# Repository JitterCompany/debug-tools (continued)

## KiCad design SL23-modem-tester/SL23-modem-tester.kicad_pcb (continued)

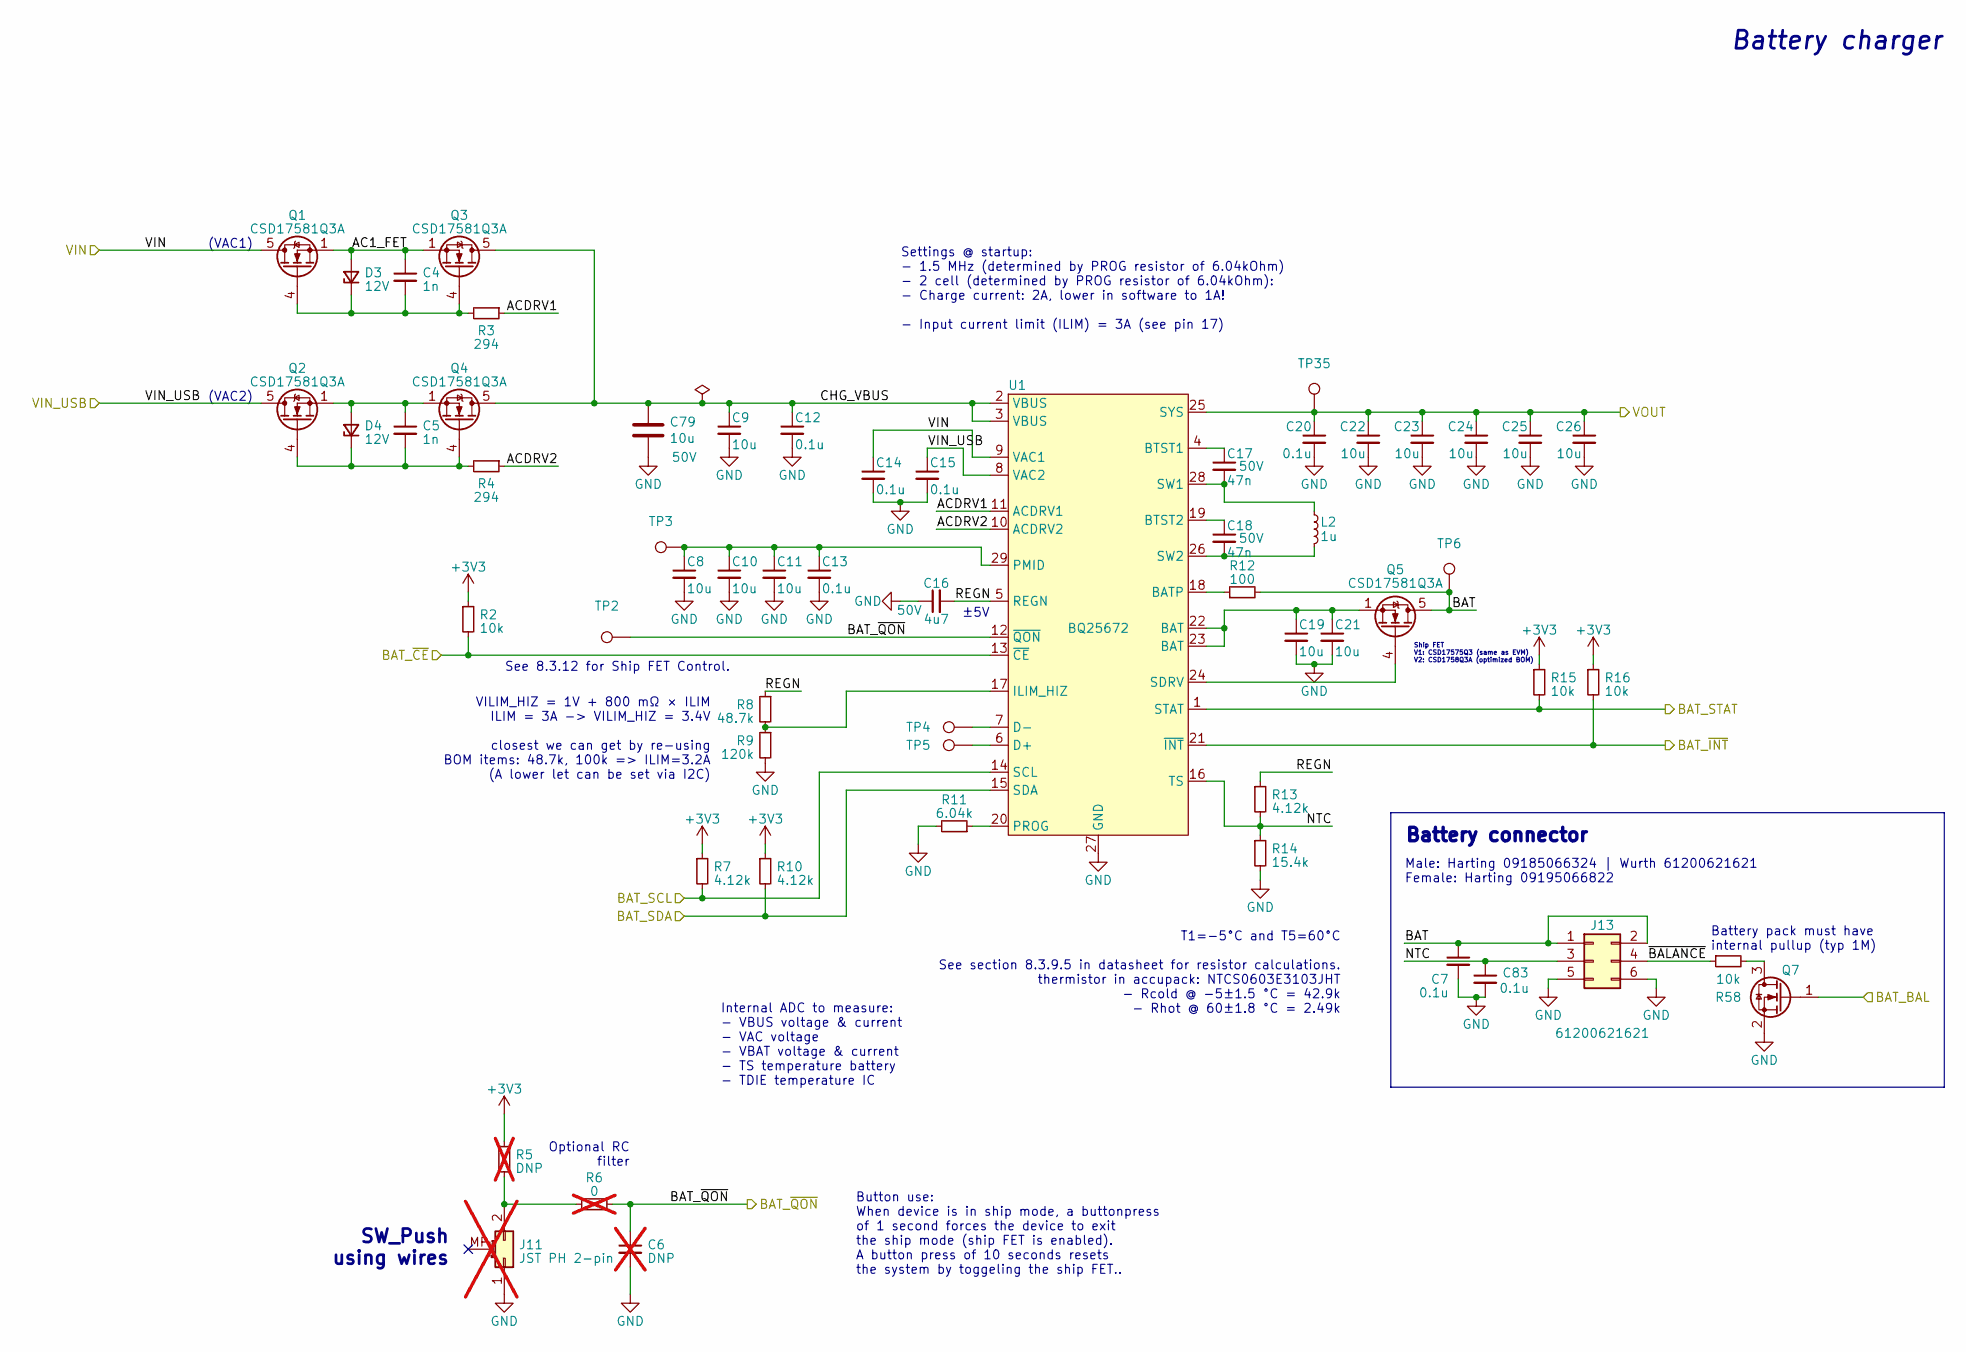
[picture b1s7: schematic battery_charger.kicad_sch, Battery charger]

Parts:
C4, C5: 1n; C_0603_1608Metric; rating 50V; MPN CGA3E2X7R1H102K080AA; Mouser 810-CGA3E2X7R1H102K
C6: DNP; C_0603_1608Metric; not fitted
C7, C12, C13, C14, C15, C20, C83: 0.1u; C_0603_1608Metric; rating 50V; MPN CGA3E2X7R1H104K080AA; Mouser 810-CGA3E2X7R1H104K
C8, C9, C10, C11, C19, C21, C22, C23, C24, C25, C26: 10u; C_0805_2012Metric; rating 50V; MPN GRM21BR61H106KE43L; Mouser 81-GRM21BR61H106KE3L
C16: 4u7; C_0805_2012Metric; rating 50V; MPN GRM21BZ71H475KE15K; Mouser 81-GRM21BZ71H475KE5K
C17, C18: 47n; C_0603_1608Metric; rating 50V; MPN CGA3E2X7R1H473K080AA; Mouser 810-CGA3E2X7R1H473K
C79: 10u; C_1210_3225Metric; rating 50V; MPN CL32A106KBJNNNE; Mouser 187-CL32A106KBJNNNE
D3, D4: 12V; D_SOD-523; MPN BZT52C12T-7; Mouser 621-BZT52C12T-7
J11: JST PH 2-pin; JST_PH_B2B-PH-SM4-TB_1x02-1MP_P2.00mm_Vertical; MPN B2B-PH-SM4-TB; Farnell 9492534; not fitted
J13: 61200621621; IDC_Header_2x03_P2.54mm_Vertical_Male; MPN 61200621621; Mouser 710-61200621621
L2: 1u; L_TDK_SPM6530; MPN SPM6530T-1R0M120; Mouser 810-SPM6530T-1R0M120
Q1, Q2, Q3, Q4, Q5: CSD17581Q3A; CSD17552Q3A; MPN CSD17581Q3A; Mouser 595-CSD17581Q3A
Q7: BSS138BK,215; SOT-23; MPN BSS138BK,215; Farnell 2053833
R2, R15, R16, R58: 10k; R_0603_1608Metric; rating 1%; MPN CRCW060310K0FKEAHP; Mouser 71-CRCW060310K0FKEAH
R3, R4: 294; R_0603_1608Metric; rating 1%; MPN CRCW0603294RFKEA; Mouser 71-CRCW0603-294-E3
R5: DNP; R_0603_1608Metric; not fitted
R6: 0; R_0603_1608Metric; rating 1%; MPN RC0603FR-070RL; Mouser 603-RC0603FR-070RL; not fitted
R7, R10, R13: 4.12k; R_0603_1608Metric; rating 1%
R8: 48.7k; R_0603_1608Metric; rating 1%
R9: 120k; R_0603_1608Metric; rating 1%
R11: 6.04k; R_0603_1608Metric; rating 1%; MPN CRCW06036K04FKEAC; Mouser 71-CRCW06036K04FKEAC
R12: 100; R_0603_1608Metric; rating 1%; MPN CRCW0603100RFKEAC; Mouser 71-CRCW0603100RFKEAC
R14: 15.4k; R_0603_1608Metric; rating 1%; MPN CRCW060315K4FKEB; Mouser 71-CRCW060315K4FKEB
TP2, TP3, TP6, TP35: TestPoint; TestPoint_THTPad_D1.0mm_Drill0.5mm
TP4, TP5: TestPoint; TestPoint_Pad_D1.0mm
U1: BQ25672; TI_VQFN-HR-29-RQM; MPN BQ25672RQMR; Mouser 595-BQ25672RQMR

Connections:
+3V3: R2.1, R5.1, R7.1, R10.1, R15.1, R16.1; also elsewhere on the board
/BAT_BAL: Q7.1 (G); also elsewhere on the board
/BAT_SCL: R7.2, U1.14 (SCL); also elsewhere on the board
/BAT_SDA: R10.2, U1.15 (SDA); also elsewhere on the board
/BAT_STAT: R15.2, U1.1 (STAT); also elsewhere on the board
/BAT_~CE: R2.2, U1.13 (~CE); also elsewhere on the board
/BAT_~INT: R16.2, U1.21 (~INT); also elsewhere on the board
/BAT_~QON: C6.1, R6.2, TP2.1 (1_1), U1.12 (~QON); also elsewhere on the board
/Battery Charger/AC1_FET: C4.1, D3.2 (A), Q1.1 (S), Q1.2 (S), Q1.3 (S), Q3.1 (S), Q3.2 (S), Q3.3 (S)
/Battery Charger/ACDRV1: R3.1, U1.11 (ACDRV1)
/Battery Charger/ACDRV2: R4.1, U1.10 (ACDRV2)
/Battery Charger/BAT: C7.1, J13.1, J13.2, Q5.5 (D), R12.2, TP6.1 (1_1)
/Battery Charger/CHG_VBUS: C9.1, C12.1, C79.1, Q3.5 (D), Q4.5 (D), U1.2 (VBUS), U1.3 (VBUS)
/Battery Charger/NTC: C83.1, J13.3, R13.2, R14.1, U1.16 (TS)
/Battery Charger/REGN: C16.2, R8.1, R13.1, U1.5 (REGN)
/Battery Charger/VIN: C14.1, Q1.5 (D), U1.9 (VAC1); also elsewhere on the board
/Battery Charger/~BALANCE: J13.4, R58.1
/VSYS: C20.1, C22.1, C23.1, C24.1, C25.1, C26.1, TP35.1 (1_1), U1.25 (SYS); also elsewhere on the board
GND: C6.2, C7.2, C8.2, C9.2, C10.2, C11.2, C12.2, C13.2, C14.2, C15.2, C16.1, C19.2, C20.2, C21.2, C22.2, C23.2, C24.2, C25.2, C26.2, C79.2, C83.2, J11.1, J13.5, J13.6, Q7.2 (S), R9.2, R11.2, R14.2, U1.27 (GND); also elsewhere on the board
unnamed: C19.1, C21.1, Q5.1 (S), Q5.2 (S), Q5.3 (S), U1.22 (BAT), U1.23 (BAT)
unnamed: C4.2, D3.1 (K), Q1.4 (G), Q3.4 (G), R3.2
unnamed: C5.1, D4.2 (A), Q2.1 (S), Q2.2 (S), Q2.3 (S), Q4.1 (S), Q4.2 (S), Q4.3 (S)
unnamed: C5.2, D4.1 (K), Q2.4 (G), Q4.4 (G), R4.2
unnamed: J11.2, R5.2, R6.1
unnamed: Q5.4 (G), U1.24 (SDRV)
unnamed: Q7.3 (D), R58.2
unnamed: R12.1, U1.18 (BATP)
unnamed: C17.1, U1.4 (BTST1)
unnamed: C18.1, U1.19 (BTST2)
unnamed: TP5.1 (1_1), U1.6 (D+)
unnamed: TP4.1 (1_1), U1.7 (D-)
unnamed: R8.2, R9.1, U1.17 (ILIM_HIZ)
unnamed: C8.1, C10.1, C11.1, C13.1, TP3.1 (1_1), U1.29 (PMID)
unnamed: R11.1, U1.20 (PROG)
unnamed: C17.2, L2.1, U1.28 (SW1)
unnamed: C18.2, L2.2, U1.26 (SW2)
VBUS: C15.1, Q2.5 (D), U1.8 (VAC2); also elsewhere on the board

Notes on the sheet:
Internal ADC to measure: - VBUS voltage & current - VAC voltage - VBAT voltage & current - TS temperature battery - TDIE temperature IC
Optional RC filter
SW_Push using wires
Button use: When device is in ship mode, a buttonpress of 1 second forces the device to exit the ship mode (ship FET is enabled). A button press of 10 seconds resets the system by toggeling the ship FET..
(VAC1)
T1=-5°C and T5=60°C See section 8.3.9.5 in datasheet for resistor calculations. thermistor in accupack: NTCS0603E3103JHT - Rcold @ -5±1.5 °C = 42.9k - Rhot @ 60±1.8 °C = 2.49k
Male: Harting 09185066324 | Wurth 61200621621 Female: Harting 09195066822
(VAC2)
Ship FET V1: CSD17575Q3 (same as EVM) V2: CSD1758Q3A (optimized BOM)
±5V
VILIM_HIZ = 1V + 800 mΩ × ILIM ILIM = 3A -> VILIM_HIZ = 3.4V closest we can get by re-using BOM items: 48.7k, 100k => ILIM=3.2A (A lower let can be set via I2C)
Battery pack must have internal pullup (typ 1M)
See 8.3.12 for Ship FET Control.
Battery charger
Battery connector
Settings @ startup: - 1.5 MHz (determined by PROG resistor of 6.04kOhm) - 2 cell (determined by PROG resistor of 6.04kOhm): - Charge current: 2A, lower in software to 1A! - Input current limit (ILIM) = 3A (see pin 17)

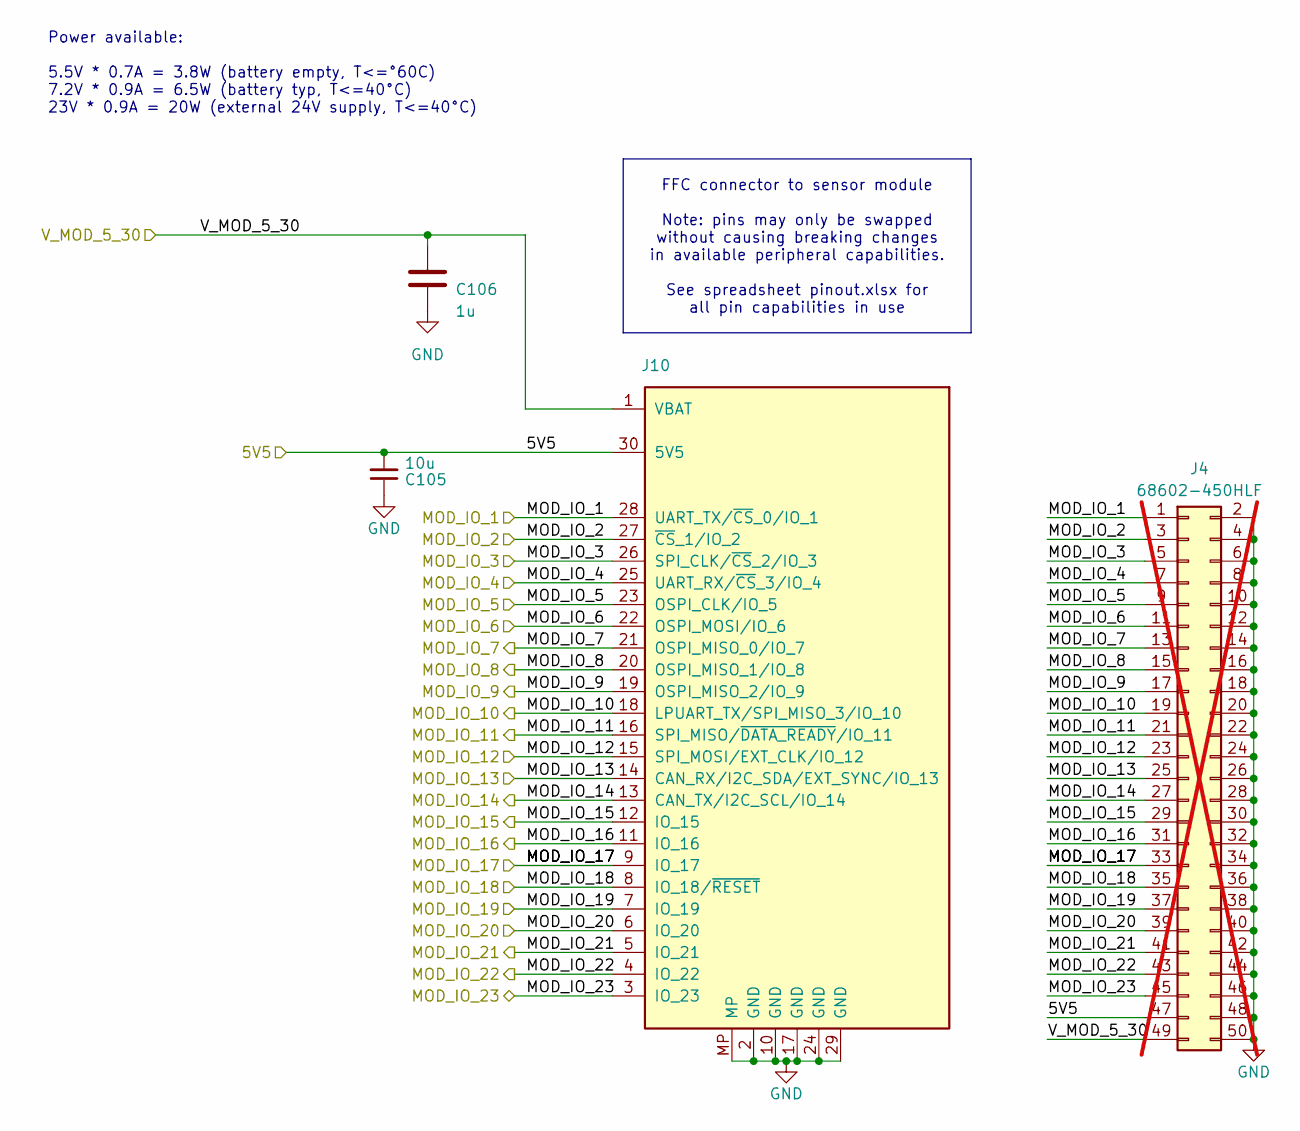
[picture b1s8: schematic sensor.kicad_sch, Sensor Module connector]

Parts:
C105: 10u; C_0805_2012Metric; rating 50V; MPN GRM21BR61H106KE43L; Mouser 81-GRM21BR61H106KE3L
C106: 1u; C_0603_1608Metric; rating 35V; MPN CGA3E1X7R1V105K080AC; Mouser 810-CGA3E1X7R1V105KC
J4: 68602-450HLF; PinHeader_2x25_P2.54mm_Vertical; MPN 68602-450HLF; not fitted
J10: Conn_01x30; Hirose_FH12-30S-0.5SH_1x15-1MP_P0.50mm_Horizontal; MPN FH12-30S-0.5SH(55); Mouser 798-FH12-30S-0.5SH55

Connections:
+5V5: C105.2, J4.47, J10.30 (5V5); also elsewhere on the board
/MCU/MOD_IO_1: J4.1, J10.28 (UART_TX/~CS_0/IO_1); also elsewhere on the board
/MCU/MOD_IO_2: J4.3, J10.27 (~CS_1/IO_2); also elsewhere on the board
/MCU/MOD_IO_3: J4.5, J10.26 (SPI_CLK/~CS_2/IO_3); also elsewhere on the board
/MCU/MOD_IO_4: J4.7, J10.25 (UART_RX/~CS_3/IO_4); also elsewhere on the board
/MCU/MOD_IO_5: J4.9, J10.23 (OSPI_CLK/IO_5); also elsewhere on the board
/MCU/MOD_IO_6: J4.11, J10.22 (OSPI_MOSI/IO_6); also elsewhere on the board
/MCU/MOD_IO_7: J4.13, J10.21 (OSPI_MISO_0/IO_7); also elsewhere on the board
/MCU/MOD_IO_8: J4.15, J10.20 (OSPI_MISO_1/IO_8); also elsewhere on the board
/MCU/MOD_IO_9: J4.17, J10.19 (OSPI_MISO_2/IO_9); also elsewhere on the board
/MCU/MOD_IO_10: J4.19, J10.18 (LPUART_TX/SPI_MISO_3/IO_10); also elsewhere on the board
/MCU/MOD_IO_11: J4.21, J10.16 (SPI_MISO/~DATA_READY/IO_11); also elsewhere on the board
/MCU/MOD_IO_12: J4.23, J10.15 (SPI_MOSI/EXT_CLK/IO_12); also elsewhere on the board
/MCU/MOD_IO_13: J4.25, J10.14 (CAN_RX/I2C_SDA/EXT_SYNC/IO_13); also elsewhere on the board
/MCU/MOD_IO_14: J4.27, J10.13 (CAN_TX/I2C_SCL/IO_14); also elsewhere on the board
/MCU/MOD_IO_15: J4.29, J10.12 (IO_15); also elsewhere on the board
/MCU/MOD_IO_16: J4.31, J10.11 (IO_16); also elsewhere on the board
/MCU/MOD_IO_17: J4.33, J10.9 (IO_17); also elsewhere on the board
/MCU/MOD_IO_18: J4.35, J10.8 (IO_18/~RESET); also elsewhere on the board
/MCU/MOD_IO_19: J4.37, J10.7 (IO_19); also elsewhere on the board
/MCU/MOD_IO_20: J4.39, J10.6 (IO_20); also elsewhere on the board
/MCU/MOD_IO_21: J4.41, J10.5 (IO_21); also elsewhere on the board
/MCU/MOD_IO_22: J4.43, J10.4 (IO_22); also elsewhere on the board
/MCU/MOD_IO_23: J4.45, J10.3 (IO_23); also elsewhere on the board
/V_MOD_5_30: C106.1, J4.49, J10.1 (VBAT); also elsewhere on the board
GND: C105.1, C106.2, J4.2, J4.4, J4.6, J4.8, J4.10, J4.12, J4.14, J4.16, J4.18, J4.20, J4.22, J4.24, J4.26, J4.28, J4.30, J4.32, J4.34, J4.36, J4.38, J4.40, J4.42, J4.44, J4.46, J4.48, J4.50, J10.2 (GND), J10.10 (GND), J10.17 (GND), J10.24 (GND), J10.29 (GND), J10.MP; also elsewhere on the board

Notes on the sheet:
Power available: 5.5V * 0.7A = 3.8W (battery empty, T<=°60C) 7.2V * 0.9A = 6.5W (battery typ, T<=40°C) 23V * 0.9A = 20W (external 24V supply, T<=40°C)
FFC connector to sensor module Note: pins may only be swapped without causing breaking changes in available peripheral capabilities. See spreadsheet pinout.xlsx for all pin capabilities in use

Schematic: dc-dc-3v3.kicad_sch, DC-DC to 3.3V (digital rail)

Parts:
C42, C43: 10u; C_1210_3225Metric; rating 50V; MPN CL32A106KBJNNNE; Mouser 187-CL32A106KBJNNNE
C44: 4u7; C_0805_2012Metric; rating 50V; MPN GRM21BZ71H475KE15K; Mouser 81-GRM21BZ71H475KE5K
C45: 1u; C_0603_1608Metric; rating 35V; MPN CGA3E1X7R1V105K080AC; Mouser 810-CGA3E1X7R1V105KC
C46, C48: 220n; C_0603_1608Metric; rating 50V; MPN CGA3E3X7R1H224K080AB; Mouser 810-CGA3E3X7R1H224K
C47, C50, C53: 0.1u; C_0603_1608Metric; rating 50V; MPN CGA3E2X7R1H104K080AA; Mouser 810-CGA3E2X7R1H104K
C49: 680p; C_0603_1608Metric; rating 50V; MPN GCM1885C1H681JA16J; Mouser 81-GCM1885C1H681JA6J
C52: 4n7; C_0603_1608Metric; rating 50V; MPN CGA3E2X7R1H472M080AA; Mouser 810-CGA3E2X7R1H472MA
C54, C55: 100u; C_1210_3225Metric; rating 6V3; MPN CL32A107MQVNNNE; Mouser 187-CL32A107MQVNNNE
C56: 47u; C_1210_3225Metric; rating 10V; MPN C3225X5R1A476M250AC; Mouser 810-C3225X5R1A476M; not fitted
C74: 560p; C_0603_1608Metric; rating 50V; MPN GCM188L81H561KA03D; Mouser 81-GCM188L81H561KA3D
C78: 2n7; C_0603_1608Metric; rating 50V; MPN CGA3E2C0G1H272J080AE; Mouser 810-CGA3E2C0G1H272J8
L4: 8.2uH; L_Wuerth_LHMI_8040; MPN 74437358082; Mouser 710-74437358082
R21, R37: 48.7k; R_0603_1608Metric; rating 1%
R28: DNP; R_0603_1608Metric; not fitted
R29: 10k; R_0603_1608Metric; rating 1%
R30: DNI; R_0603_1608Metric; rating 1%; not fitted
R31, R57: 10k; R_0603_1608Metric; rating 1%; MPN CRCW060310K0FKEAHP; Mouser 71-CRCW060310K0FKEAH
R33: 120k; R_0603_1608Metric; rating 1%; MPN CRCW0603120KFKEAC; Mouser 71-CRCW0603120KFKEAC
R34, R56: 348K; R_0603_1608Metric; rating 1%; MPN CRCW0603348KFKEA; Mouser 71-CRCW0603-348K-E3
R35: 2.2; R_0603_1608Metric; rating 1%; MPN CRCW06032R20FKEAC; Mouser 71-CRCW06032R20FKEAC
R36: 4.12k; R_0603_1608Metric; rating 1%
R38: 15.4k; R_0603_1608Metric; rating 1%
TP10, TP11, TP12: TestPoint; TestPoint_THTPad_D1.0mm_Drill0.5mm
U3: SIC473ED-T1-GE3; Vishay_MLP55-27L; MPN SIC473ED-T1-GE3; Mouser 78-SIC473ED-T1-GE3

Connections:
+3V3: C52.1, C53.1, C54.1, C55.1, C56.1, L4.2, R37.1, TP11.1 (1_1); also elsewhere on the board
/DCDC_ULTRA: R57.1; also elsewhere on the board
/POWER_GOOD_3V3: U3.2 (PGOOD); also elsewhere on the board
/Power 3V3/BOOT: C50.1, U3.4 (BOOT)
/Power 3V3/CMP: R34.1, U3.21 (COMP)
/Power 3V3/EN: R28.1, R29.2, R30.1, TP10.1 (1_1), U3.3 (EN)
/Power 3V3/FB: R37.2, R38.1, U3.22 (FB)
/Power 3V3/FSW: R21.1, R56.1, U3.24 (FSW)
/Power 3V3/ILIMIT: R33.1, U3.25 (ILIMIT)
/Power 3V3/MODE: R31.1, U3.27 (MODE)
/Power 3V3/PHASE: R35.2, U3.5 (PHASE), U3.6 (PHASE)
/Power 3V3/SS: C47.1, U3.19 (SS)
/Power 3V3/SW: L4.1, R36.2, U3.12 (SW), U3.13 (SW), U3.14 (SW)
/Power 3V3/VDD: C45.2, U3.26 (VDD)
/Power 3V3/VDRV: C44.2, U3.16 (VDRV)
/Power 3V3/VSNS: C74.1, C78.2, U3.20 (VSNS)
/Power 3V3/~DISABLE: R28.2
/VSYS: C42.1, C43.1, C46.1, C48.1, R29.1, U3.1 (VCIN), U3.7 (VIN), U3.8 (VIN), U3.29 (VIN); also elsewhere on the board
GND: C42.2, C43.2, C44.1, C45.1, C46.2, C47.2, C48.2, C49.2, C53.2, C54.2, C55.2, C56.2, R21.2, R30.2, R31.2, R33.2, R38.2, R56.2, TP12.1 (1_1), U3.9 (PGND), U3.10 (PGND), U3.11 (PGND), U3.17 (PGND), U3.23 (AGND), U3.28 (AGND), U3.30 (PGND); also elsewhere on the board
unnamed: C49.1, R34.2
unnamed: C50.2, R35.1
unnamed: C52.2, C74.2, C78.1, R36.1
unnamed: R57.2, U3.18 (ULTRASONIC)

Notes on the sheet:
DC-DC converter 5.5-30V in to 3.3V 3A out
ESR compensation
Soft-start 100nF = 16 ms
3V3 DC-DC
Settings: Power save mode, 400kHz, 5A peak limit
DC-derating: 8uF @30V, 16.5uF @12V
Output voltage setpoint Fb=0.8V > 3.33V
Note: open-drain output. needs pull-up, is located on MCU sheet.
Set high to force frequency above audio range (>20khz) in case the vibrations from switching impact the sensor readings
Note: DC-bias derated to 3x35uF @3.3V
Click to go back to power input
Compensation network Fco=58.9kHz, pm=80.9deg (Vishay PowerCAD)
No UVLO: threshold is not accurate Firmware can periodically measure the battery level and stop measuring if it becomes too low
EN pin is high voltage compatible

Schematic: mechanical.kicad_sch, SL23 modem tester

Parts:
FID1, FID2, FID3, FID4, FID5: Fiducial; Fiducial_1mm_Mask3mm
H1, H3, H4: MountingHole; MountingHole_3.2mm_M3_DIN965_Pad
H2: MountingHole_Pad; MountingHole_3.2mm_M3_DIN965_Pad
LOGO1: Jitter front; Jitter
LOGO2: Jitter back; Jitter

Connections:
GND: H1.1 (1_1), H2.1 (1_1), H3.1 (1_1), H4.1 (1_1); also elsewhere on the board

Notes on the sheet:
Top
Mounting Holes
Mechanical
Logos on PCB
Fiducials

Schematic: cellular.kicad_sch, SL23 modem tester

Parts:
C90, C91, C96: 0.1u; C_0603_1608Metric; rating 50V; MPN CGA3E2X7R1H104K080AA; Mouser 810-CGA3E2X7R1H104K
C92: 4n7; C_0603_1608Metric; rating 50V; MPN CGA3E2X7R1H472M080AA; Mouser 810-CGA3E2X7R1H472MA
C93, C95: 100u; C_1210_3225Metric; rating 6V3; MPN CL32A107MQVNNNE; Mouser 187-CL32A107MQVNNNE
C94: 4u7; C_0805_2012Metric; rating 50V; MPN GRM21BZ71H475KE15K; Mouser 81-GRM21BZ71H475KE5K
H3D1: 4G Modem; mPCIe_module
J2: MM60-EZH039-B5-R850; MPN MM60-EZH039-B5-R850; Mouser 656-MM60-EZH039-B5-R
J6: PinHeader_2x20_P2.54mm_Vertical; not fitted
J7: ‎MM60-52B1-G1-R850‎; BUS_PCI_Express_Mini_MM60-52B1-G1-R850; MPN ‎MM60-52B1-G1-R850‎; Mouser 656-MM6052B1G1R850
R50: DNP; R_0603_1608Metric; not fitted
U6: SLG59M301V; DFN200X150X80-8N; MPN SLG59M301V; Mouser 402-SLG59M301V

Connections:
+3V3: C90.1, C91.1, U6.1 (VDD), U6.3 (IN), U6.4 (IN); also elsewhere on the board
/CELLULAR_DTR: J6.5, J7.31 (PETn0); also elsewhere on the board
/CELLULAR_PWR_EN: R50.1, U6.2 (ON); also elsewhere on the board
/CELLULAR_UART_CTS: J6.1, J7.23 (PERn0); also elsewhere on the board
/CELLULAR_UART_RTS: J6.3, J7.25 (PERp0); also elsewhere on the board
/CELLULAR_UART_RX: J6.19, J7.11 (REFCLK-); also elsewhere on the board
/CELLULAR_UART_TX: J6.17, J7.13 (REFCLK+); also elsewhere on the board
/CELLULAR_~RESET: J6.9, J7.22 (~PERST); also elsewhere on the board
/Cellular Modem/3V3_PCIE: C93.1, C94.1, C95.1, C96.1, J6.39, J7.2 (+3V3AUX), J7.24 (+3V3AUX), J7.39 (+3V3AUX), J7.41 (+3V3AUX), J7.52 (+3V3AUX), U6.5 (VOUT), U6.6 (VOUT)
/Cellular Modem/LED_~WWAN: J6.7, J7.42 (~LED_WWAN)
/Cellular Modem/RI: J6.13, J7.17 (UIM_C8)
/Cellular Modem/UIM_CLK: J6.31, J7.12 (UIM_CLK)
/Cellular Modem/UIM_DATA: J6.33, J7.10 (UIM_DATA)
/Cellular Modem/UIM_VCC: J6.35, J7.8 (UIM_PWR)
/Cellular Modem/UIM_~RST: J6.29, J7.14 (~UIM_RESET)
/Cellular Modem/USB_D+: J6.23, J7.38 (USB_D+)
/Cellular Modem/USB_D-: J6.25, J7.36 (USB_D-)
/Cellular Modem/~W_DISABLE: J6.11, J7.20 (~W_DISABLE)
GND: C90.2, C91.2, C92.2, C93.2, C94.2, C95.2, C96.2, J2.1 (1_1), J6.2, J6.4, J6.6, J6.8, J6.10, J6.12, J6.14, J6.16, J6.18, J6.20, J6.22, J6.24, J6.26, J6.28, J6.30, J6.32, J6.34, J6.36, J6.38, J6.40, J7.4 (GND), J7.9 (GND), J7.15 (GND), J7.18 (GND), J7.21 (GND), J7.26 (GND), J7.27 (GND), J7.29 (GND), J7.34 (GND), J7.35 (GND), J7.37 (GND), J7.40 (GND), J7.43 (GND), J7.50 (GND), J7.MP, R50.2, U6.8 (GND); also elsewhere on the board
unnamed: C92.1, U6.7 (CAP)

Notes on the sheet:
Power switch
mPCIE slot
mPCIE modem should have its own onboard SIM card
For some modules (e.g. Quectel EC2x) this determines if the module is allowed to enter sleep mode (low=never sleep)
On > 0.85V
no SIM slot
Easily serviceable / upgradeable: most modems in mini-PCIe form-factor should work (4G / LTE-M / 5G / etc)
Controls power to mini-PCIE slot
Slew rate control 4.7nF = ca 2.5 V/ms I_{inrush} = 200uF * 2.5 V/ms = 500mA
SLG59M301V has internal pulldown (4M)
Quectel EC25 current: max 800mA, 2.7A peak (2G) mPCIE spec: max 1100mA, 2.75A peak
Cellular
Derating: 2x64uF @ 3.3V
I2C

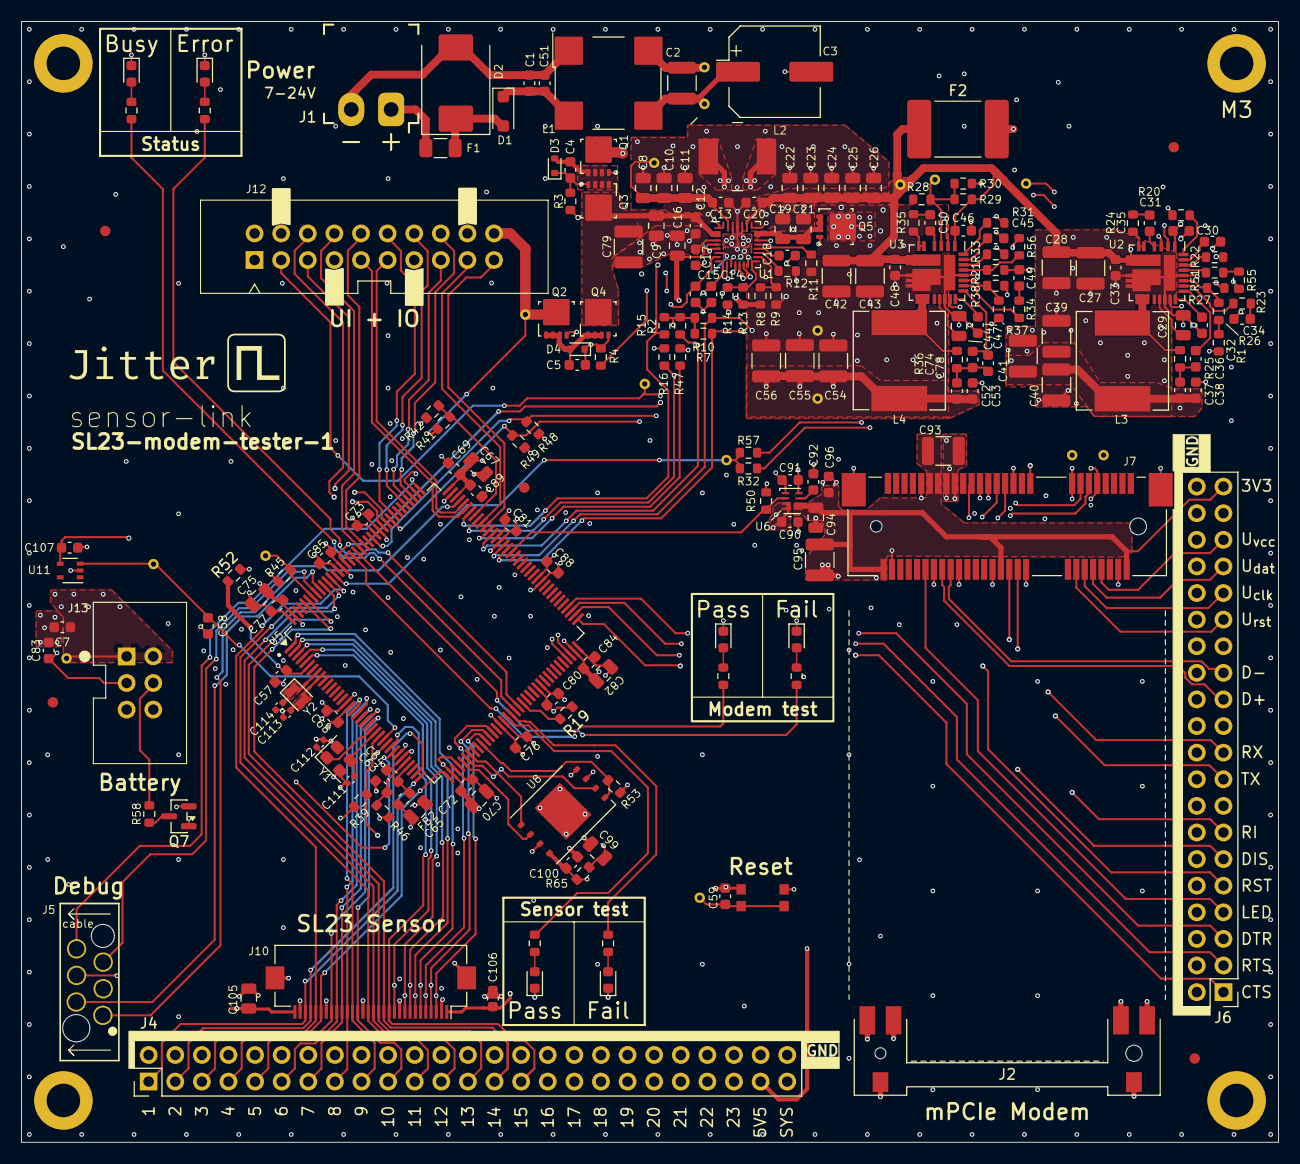
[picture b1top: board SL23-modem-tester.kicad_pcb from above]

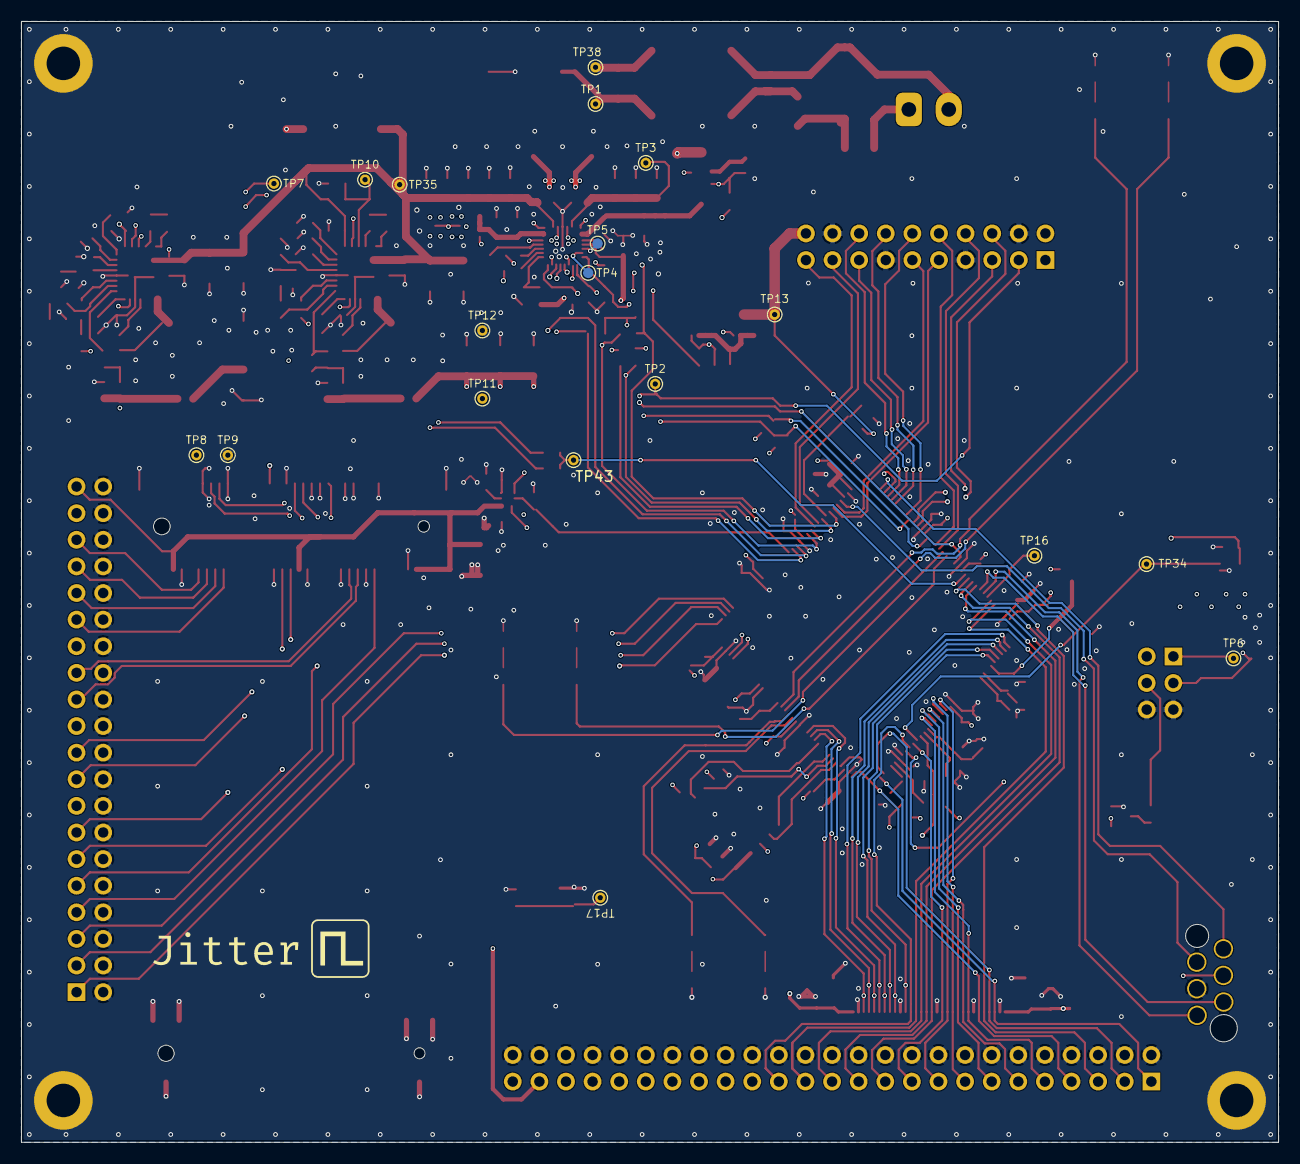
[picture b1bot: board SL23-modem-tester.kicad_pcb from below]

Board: 4 copper layers, 120.0 x 107.0 mm, 229 parts (20 on the bottom side), 170 nets.

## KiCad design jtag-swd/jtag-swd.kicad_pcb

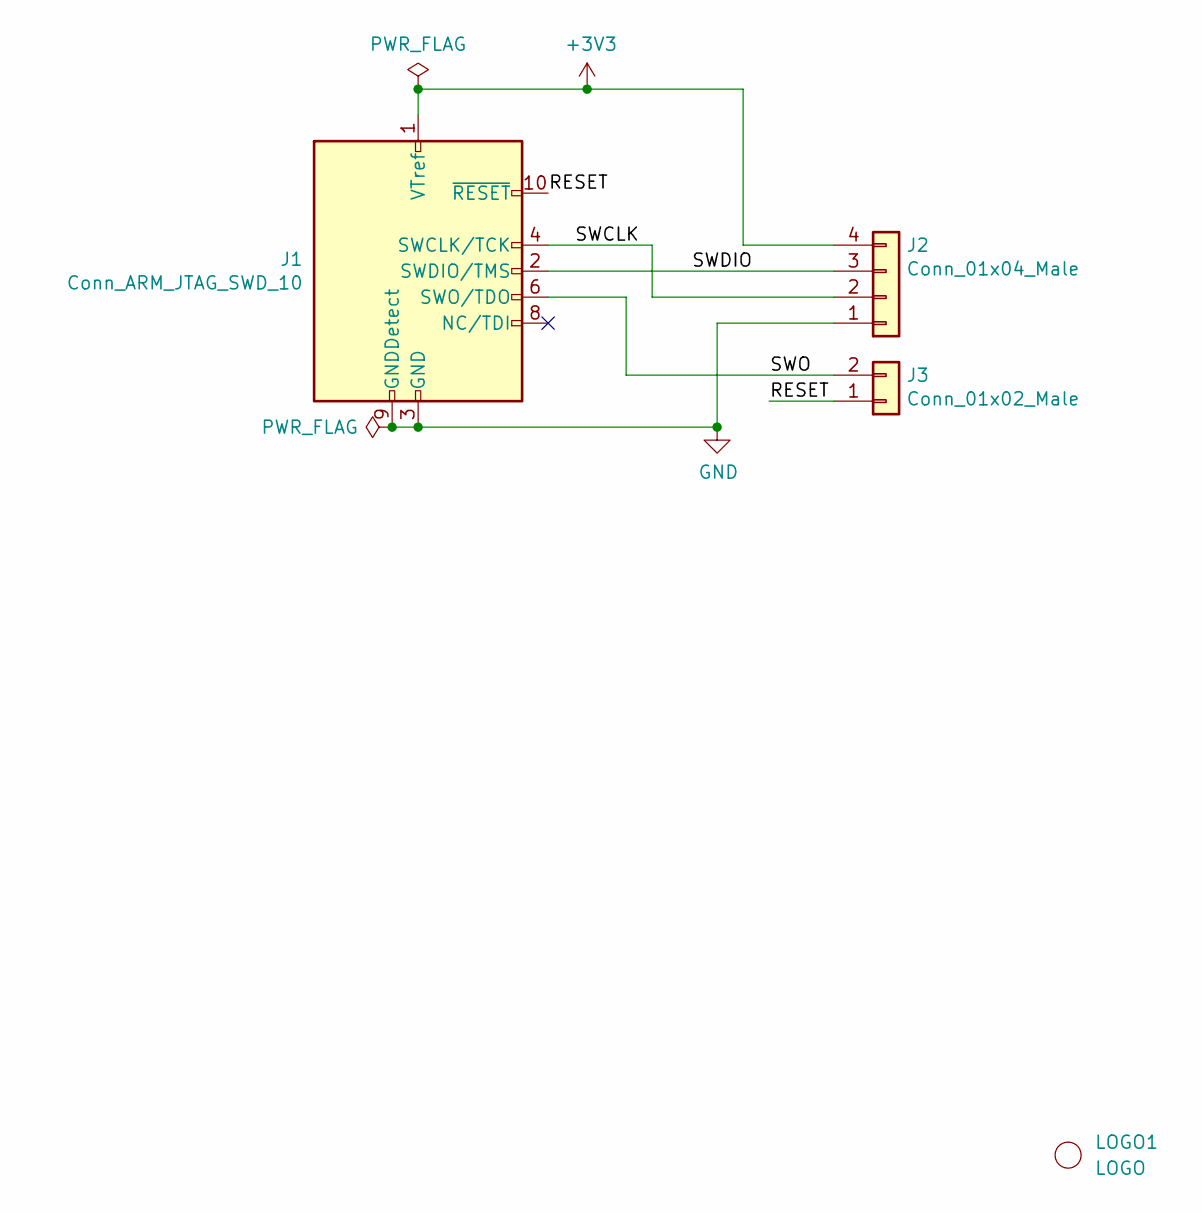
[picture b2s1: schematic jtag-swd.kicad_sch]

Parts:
J1: Conn_ARM_JTAG_SWD_10; PinSocket_2x05_P1.27mm_Vertical_Mirrored_Y; MPN SFMC-105-01-L-D
J2: Conn_01x04_Male; PinHeader_1x04_P2.54mm_Horizontal
J3: Conn_01x02_Male; PinHeader_1x02_P2.54mm_Vertical
LOGO1: LOGO; Jitter-micro

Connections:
+3V3: J1.1 (VTref), J2.4
/RESET: J1.10 (~RESET), J3.1
/SWCLK: J1.4 (SWCLK/TCK), J2.2
/SWDIO: J1.2 (SWDIO/TMS), J2.3
/SWO: J1.6 (SWO/TDO), J3.2
GND: J1.3 (GND), J1.5 (GND), J1.9 (GNDDetect), J2.1

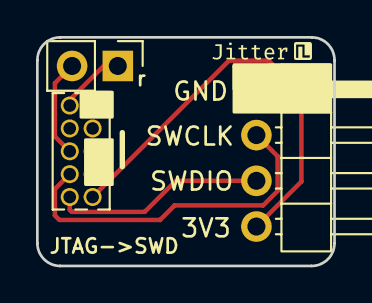
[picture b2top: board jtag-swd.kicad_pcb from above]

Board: 2 copper layers, 16.5 x 12.7 mm, 4 parts (0 on the bottom side), 6 nets.

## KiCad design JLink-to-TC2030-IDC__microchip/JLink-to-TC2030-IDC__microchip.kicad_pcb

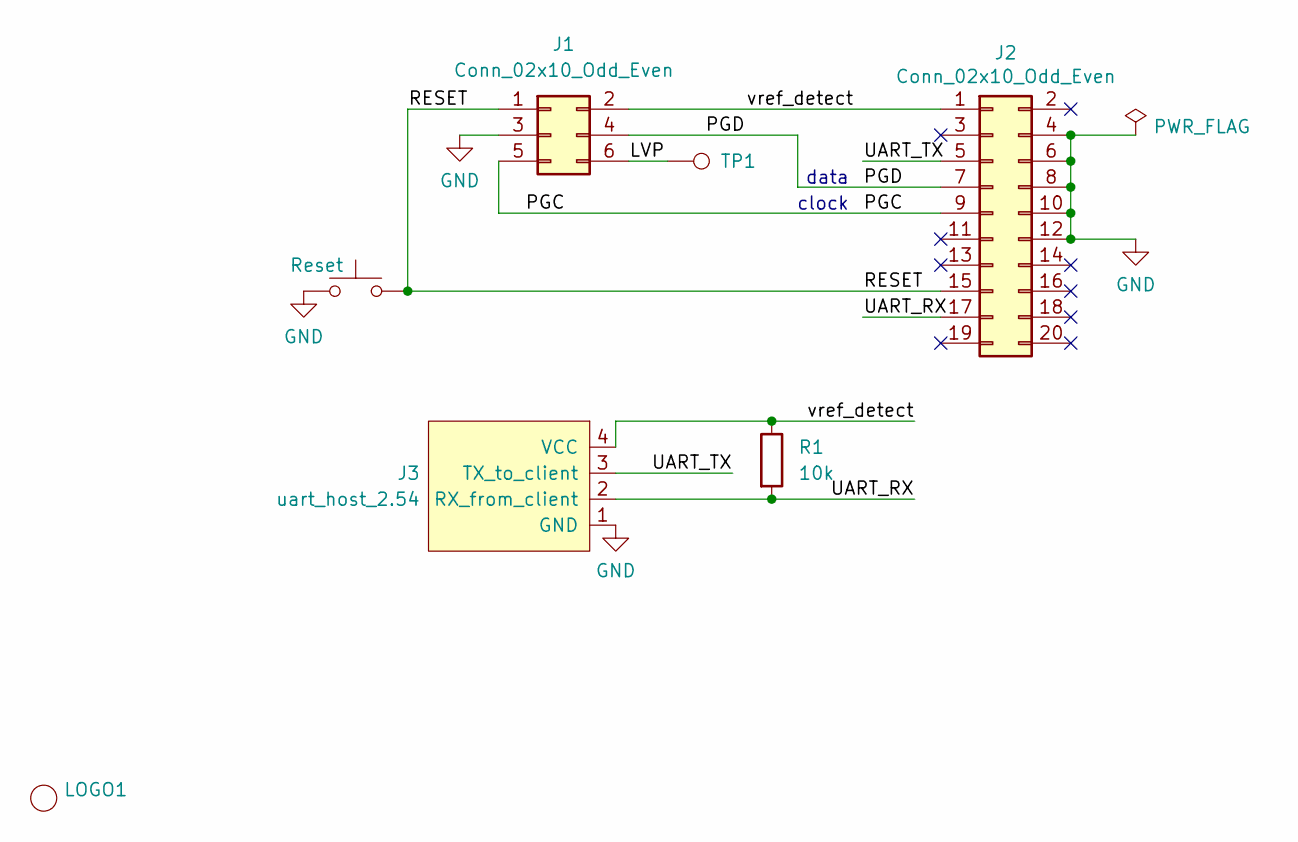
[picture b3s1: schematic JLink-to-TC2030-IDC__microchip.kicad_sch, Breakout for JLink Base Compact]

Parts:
J1: Conn_02x10_Odd_Even; IDC-Header_2x03_P2.54mm_Vertical; MPN BHR-06-VUA
J2: Conn_02x10_Odd_Even; JLink_PinHeader_2x10_2.54_Horizontal
J3: uart_host_2.54; PinHeader_1x04_P2.54mm_Vertical
LOGO1: LOGO; JitterLogo
R1: 10k; R_0603_1608Metric
SW1: Reset; SW_SPST_EVQPE1
TP1: DNI; TestPoint_THTPad_D1.0mm_Drill0.5mm

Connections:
/LVP: J1.6, TP1.1 (1_1)
/PGC: J1.5, J2.9
/PGD: J1.4, J2.7
/RESET: J1.1, J2.15, SW1.2
/UART_RX: J2.17, J3.2 (RX_from_client), R1.2
/UART_TX: J2.5, J3.3 (TX_to_client)
/vref_detect: J1.2, J2.1, J3.4 (VCC), R1.1
GND: J1.3, J2.4, J2.6, J2.8, J2.10, J2.12, J3.1 (GND), SW1.1

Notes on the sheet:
clock
data

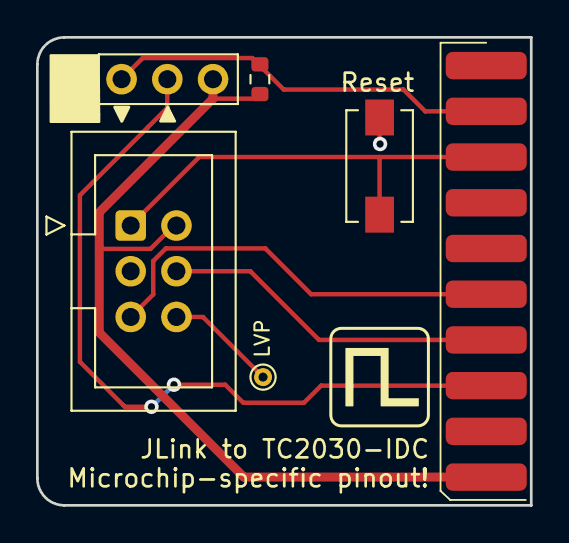
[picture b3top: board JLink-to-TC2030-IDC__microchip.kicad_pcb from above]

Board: 2 copper layers, 27.4 x 26.0 mm, 7 parts (0 on the bottom side), 8 nets.

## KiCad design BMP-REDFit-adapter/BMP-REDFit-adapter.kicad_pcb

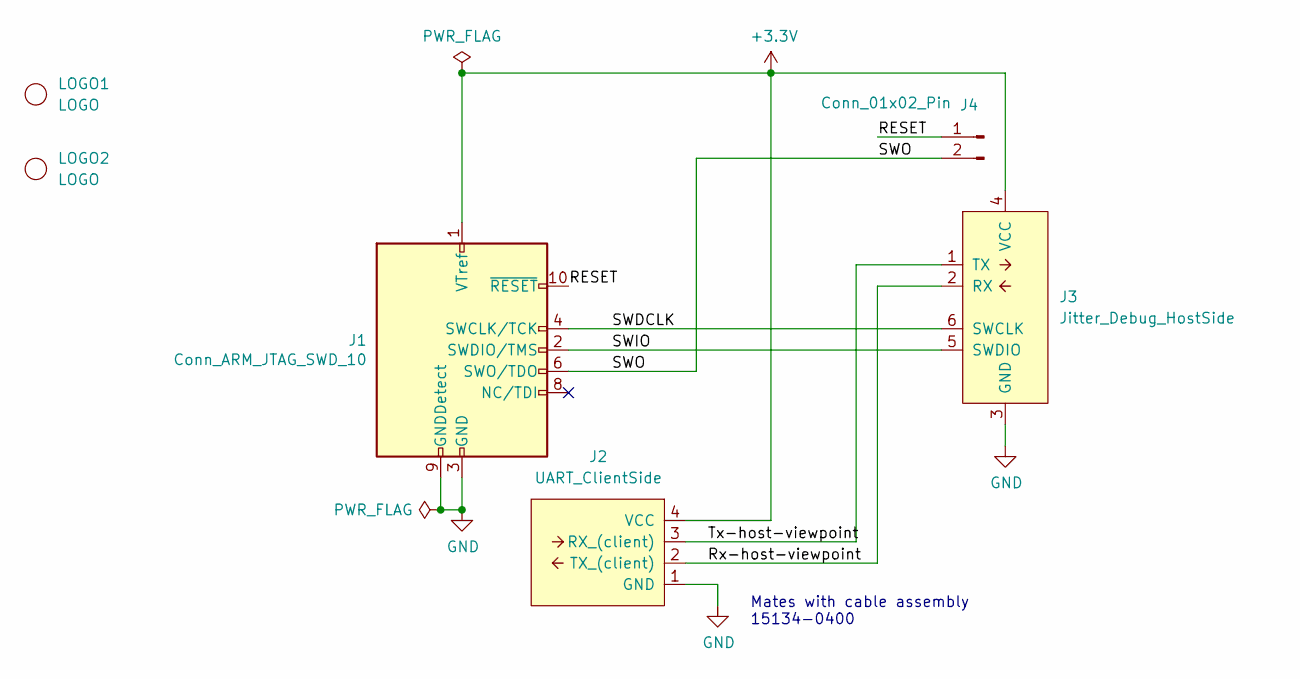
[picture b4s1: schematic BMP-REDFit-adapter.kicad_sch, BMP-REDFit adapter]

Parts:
J1: Conn_ARM_JTAG_SWD_10; connector_jtag_10pin-female-mirrored; MPN FLE-105-01-G-DV; Farnell 1667672
J2: UART_ClientSide; Molex_PicoBlade_53261-0471_1x04-1MP_P1.25mm_Horizontal; MPN 53261-0471; Farnell 1125374
J3: Jitter_Debug_HostSide; WR-WST_REDFIT-6-pins_490107670612-adapter_to_pcb
J4: Conn_01x02_Pin; PinHeader_1x02_P2.54mm_Vertical
LOGO1: LOGO; Jitter-mini
LOGO2: LOGO; JitterLogo

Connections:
+3.3V: J1.1 (VTref), J2.4 (VCC), J3.4 (VCC)
/RESET: J1.10 (~RESET), J4.1
/Rx-host-viewpoint: J2.2 (TX_(client)), J3.2 (RX)
/SWDCLK: J1.4 (SWCLK/TCK), J3.6 (SWCLK)
/SWIO: J1.2 (SWDIO/TMS), J3.5 (SWDIO)
/SWO: J1.6 (SWO/TDO), J4.2
/Tx-host-viewpoint: J2.3 (RX_(client)), J3.1 (TX)
GND: J1.3 (GND), J1.5 (GND), J1.9 (GNDDetect), J2.1 (GND), J3.3 (GND)

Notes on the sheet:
Mates with cable assembly 15134-0400

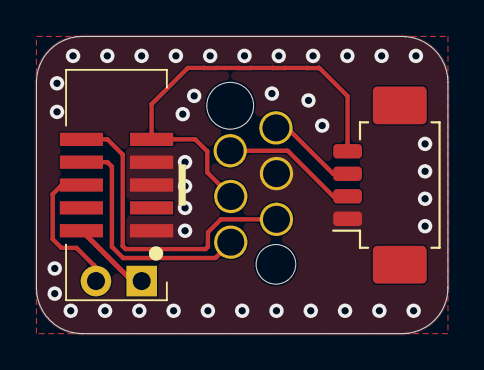
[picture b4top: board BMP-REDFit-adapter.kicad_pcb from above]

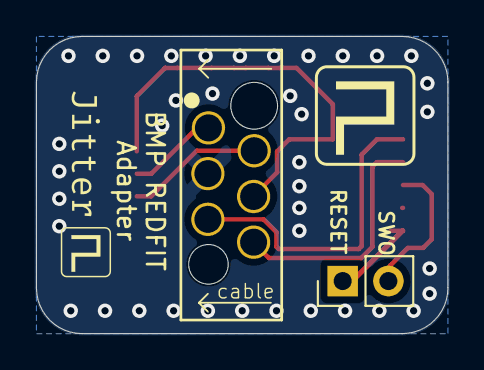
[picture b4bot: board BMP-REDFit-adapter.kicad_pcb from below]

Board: 2 copper layers, 22.9 x 16.5 mm, 6 parts (4 on the bottom side), 8 nets.
